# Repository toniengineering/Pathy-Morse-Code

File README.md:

Pathy is a small morse code device used to blink morse code with the click of a button. I wanted to try learning morse code a bit and having buttons where I can look at the light and whether it was a long blink or small blink I should be able to translate it. Also having a couple of premade buttons sounded cool like yes and no, they are always used and quick to learn. I decided to do a project like this because of how much I know how to code and I have not worked with pcbs before so I mostly wanted this to be about the pcbs design.

BOM:

 |Name        |Purpose      |Quantity                                                    |Total Cost (USD)|Link                                                                                                                                                                                                                                                                                                                                                                                                                                                                                                                                                                                                                                                                                                                                              |Distributor|
|------------|-------------|------------------------------------------------------------|----------------|--------------------------------------------------------------------------------------------------------------------------------------------------------------------------------------------------------------------------------------------------------------------------------------------------------------------------------------------------------------------------------------------------------------------------------------------------------------------------------------------------------------------------------------------------------------------------------------------------------------------------------------------------------------------------------------------------------------------------------------------------|----------|
|Resistors   |Keep the lights from burning out.|600                                     |2.56            |https://www.aliexpress.us/item/3256803089832670.html?spm=a2g0o.productlist.main.24.2bd0EUb3EUb3c2&aem_p4p_detail=202606111512134497445139988470000354431&algo_pvid=38693eea-0157-403c-9d6e-a28d685c63fa&algo_exp_id=38693eea-0157-403c-9d6e-a28d685c63fa-23&pdp_ext_f=%7B%22order%22%3A%22364%22%2C%22eval%22%3A%221%22%2C%22fromPage%22%3A%22search%22%7D&pdp_npi=6%40dis%21USD%212.56%212.56%21%21%212.56%212.56%21%402101e80317812159332583749eac1f%2112000030358692951%21sea%21US%210%21ABX%211%210%21n_tag%3A-29910%3Bd%3A27d5160c%3Bm03_new_user%3A-29895&curPageLogUid=imZQpjGjPpkV&utparam-url=scene%3Asearch%7Cquery_from%3A%7Cx_object_id%3A1005003276147422%7C_p_origin_prod%3A&search_p4p_id=202606111512134497445139988470000354431_7|Aliexpress|
|Xiao rp2040 |Power on the electronics for the pcb|1                                    |11.73           |https://www.aliexpress.us/item/3256807240972277.html?spm=a2g0o.productlist.0.0.1bc9379c5csoli&gatewayAdapt=glo2usa                                                                                                                                                                                                                                                                                                                                                                                                                                                                                                                                                                                                                                |Aliexpress|
|Keycaps     |To put on top of the key switches|8                                       |2.86            |https://www.aliexpress.us/item/3256810033104022.html?spm=a2g0o.productlist.main.35.52ceLShpLShp82&utparam-url=scene%3Asearch%7Cquery_from%3Apc_back_same_best%7Cx_object_id%3A1005010219418774%7C_p_origin_prod%3A&algo_pvid=1bf07656-f37d-443e-93b2-8f0d7e1feb6e&algo_exp_id=1bf07656-f37d-443e-93b2-8f0d7e1feb6e&pdp_ext_f=%7B%22order%22%3A%2252%22%2C%22fromPage%22%3A%22search%22%7D&pdp_npi=6%40dis%21USD%212.87%212.87%21%21%2119.37%2119.37%21%402103128917812050536722227e44ff%2112000051568483121%21sea%21US%210%21ABX%211%210%21n_tag%3A-29910%3Bd%3A27d5160c%3Bm03_new_user%3A-29895&gatewayAdapt=4itemAdapt|                                                                                                                         |Aliexpress|
|Key switches|So I can click it to make the lights blink the way I want.|10             |3.05            |https://www.aliexpress.us/item/3256810491600900.html?spm=a2g0n.shopcart.0.0.5f7438daR4t9Y4&mp=1&pdp_npi=6%40dis%21USD%21USD+6.10%21USD+3.05%21%21USD+3.05%21%21%21%402101e2b617812066391243237ea891%2112000053164128840%21ct%21US%21-1%21%211%210%21&gatewayAdapt=glo2usa                                                                                                                                                                                                                                                                                                                                                                                                                                                                         |Aliexpress|
|5mm LED     |The blinking every time I press a key switch|100                          |1.36            |https://www.aliexpress.us/item/3256805522196114.html?spm=a2g0o.productlist.main.13.2ed12c10o9N1kK&utparam-url=scene%3Asearch%7Cquery_from%3Apc_back_same_best%7Cx_object_id%3A1005005708510866%7C_p_origin_prod%3A&algo_pvid=f5e9e0e2-db45-43fd-8563-3f353d0a8ab3&algo_exp_id=f5e9e0e2-db45-43fd-8563-3f353d0a8ab3&pdp_ext_f=%7B%22order%22%3A%2214320%22%2C%22fromPage%22%3A%22search%22%7D&pdp_npi=6%40dis%21USD%211.36%211.36%21%21%219.14%219.14%21%402103128917812047619552862e44ff%2112000034078716878%21sea%21US%210%21ABX%211%210%21n_tag%3A-29910%3Bd%3A27d5160c%3Bm03_new_user%3A-29895&gatewayAdapt=4itemAdapt|                                                                                                                        |Aliexpress|
[convertcsv.md](https://github.com/user-attachments/files/28859285/convertcsv.md)

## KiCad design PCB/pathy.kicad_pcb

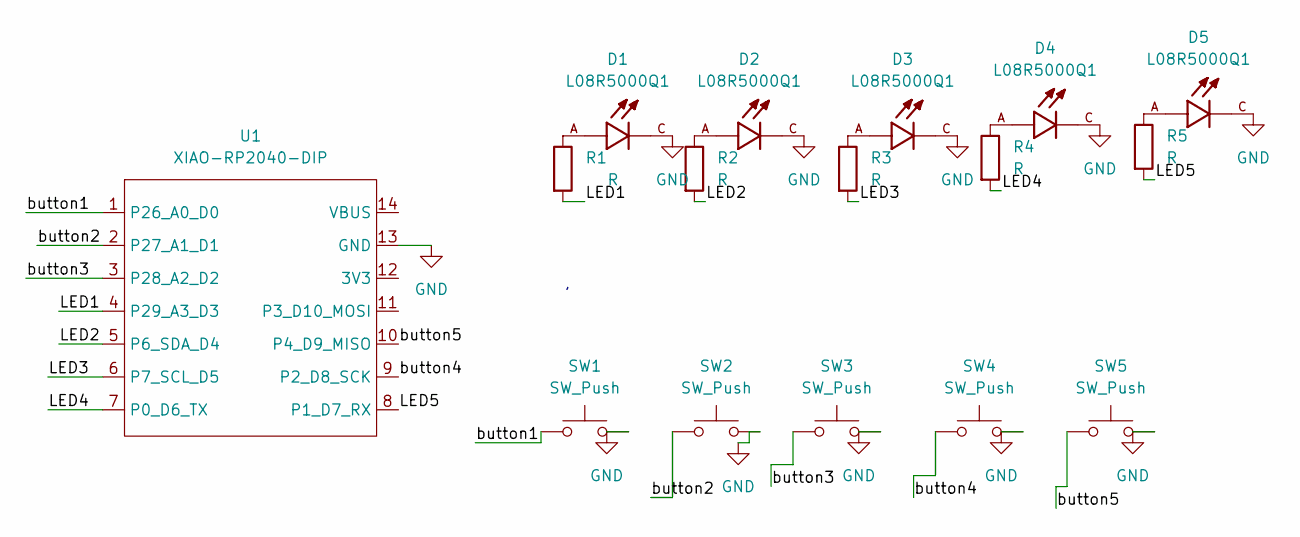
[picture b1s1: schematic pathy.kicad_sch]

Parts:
D1, D2, D3, D4, D5: L08R5000Q1; LEDRD254W57D500H1070; PARTREV NA
R1, R2, R3, R4, R5: R; R_Axial_DIN0204_L3.6mm_D1.6mm_P5.08mm_Horizontal
SW1, SW2, SW3, SW4, SW5: SW_Push; SW_Cherry_MX_1.00u_PCB
U1: XIAO-RP2040-DIP

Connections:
/LED1: R1.2, U1.4 (P29_A3_D3)
/LED2: R2.2, U1.5 (P6_SDA_D4)
/LED3: R3.2, U1.6 (P7_SCL_D5)
/LED4: R4.2, U1.7 (P0_D6_TX)
/LED5: R5.2, U1.8 (P1_D7_RX)
/button1: SW1.1, U1.1 (P26_A0_D0)
/button2: SW2.1, U1.2 (P27_A1_D1)
/button3: SW3.1, U1.3 (P28_A2_D2)
/button4: SW4.1, U1.9 (P2_D8_SCK)
/button5: SW5.1, U1.10 (P4_D9_MISO)
GND: D1.C, D2.C, D3.C, D4.C, D5.C, SW1.2, SW2.2, SW3.2, SW4.2, SW5.2, U1.13 (GND)
unnamed: D1.A, R1.1
unnamed: D2.A, R2.1
unnamed: D3.A, R3.1
unnamed: D4.A, R4.1
unnamed: D5.A, R5.1

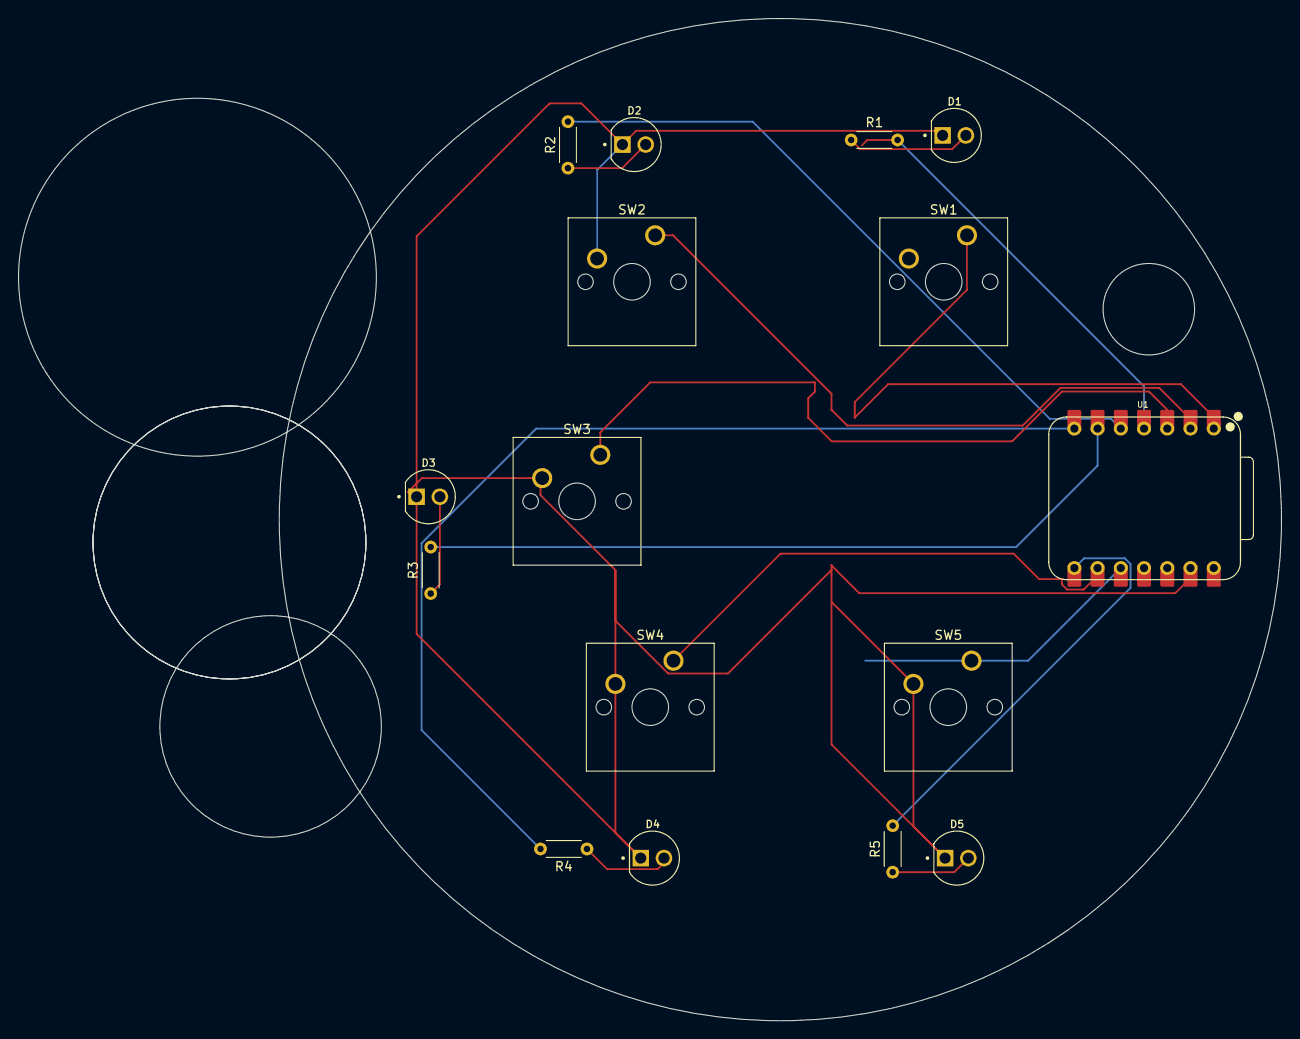
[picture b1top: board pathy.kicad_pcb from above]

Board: 2 copper layers, 138.1 x 109.6 mm, 16 parts (0 on the bottom side), 16 nets.

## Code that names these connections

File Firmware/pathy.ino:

#define BUT1 D0
#define BUT2 D1
#define BUT3 D2
#define BUT4 D8
#define BUT5 D9


#define LED1 D3
#define LED2 D4
#define LED3 D5
#define LED4 D6
#define LED5 D7

void setup() {
pinMode(BUT1, INPUT_PULLUP);
pinMode(BUT2, INPUT_PULLUP);
pinMode(BUT3, INPUT_PULLUP);
pinMode(BUT4, INPUT_PULLUP);
pinMode(BUT5, INPUT_PULLUP);


pinMode(LED1, OUTPUT);
pinMode(LED2, OUTPUT);
pinMode(LED3, OUTPUT);
pinMode(LED4, OUTPUT);
pinMode(LED5, OUTPUT);

}

void loop() {
  //small dash
 if (digitalRead(BUT1) == LOW) {
 digitalWrite(LED1, HIGH);
 delay(500);
 digitalWrite(LED1, LOW);
 delay(1000);
 }
 // long dash
 if
 (digitalRead(BUT2) == LOW) {
 digitalWrite(LED2, HIGH);
 delay(1000);
 digitalWrite(LED2, LOW);
 delay(1000);
 }
 //s
 if 
  (digitalRead(BUT3) == LOW) {
 digitalWrite(LED3, HIGH);
 delay(500);
 digitalWrite(LED3, LOW);
 delay(500);
 digitalWrite(LED3, HIGH);
delay(500);
digitalWrite(LED3, LOW);
delay(500);
digitalWrite(LED3, HIGH);
 delay(500);
 digitalWrite(LED3, LOW);
 delay(500);
 //o
 digitalWrite(LED3, HIGH);
 delay(1000);
 digitalWrite(LED3, LOW);
 delay(500);
  digitalWrite(LED3, HIGH);
 delay(1000);
 digitalWrite(LED3, LOW);
 delay(500);
  digitalWrite(LED3, HIGH);
 delay(1000);
 digitalWrite(LED3, LOW);
 delay(500);
 //s
 (digitalRead(BUT3) == LOW) ;
 digitalWrite(LED3, HIGH);
 delay(500);
 digitalWrite(LED3, LOW);
 delay(500);
 digitalWrite(LED3, HIGH);
delay(500);
digitalWrite(LED3, LOW);
delay(500);
digitalWrite(LED3, HIGH);
 delay(500);
 digitalWrite(LED3, LOW);
 delay(500);
  }
 //yes
if
  (digitalRead(BUT4) == LOW) {
 digitalWrite(LED4, HIGH);
 delay(1000);
 digitalWrite(LED4, LOW);
 delay(500);
 digitalWrite(LED4, HIGH);
 delay(500);
 digitalWrite(LED4, LOW);
 delay(500);
 digitalWrite(LED4, HIGH);
 delay(1000);
 digitalWrite(LED4, LOW);
 delay(500);
 digitalWrite(LED4, HIGH);
 delay(1000);
 digitalWrite(LED4, LOW);
 delay(1000);
 digitalWrite(LED4, HIGH);
 delay(500);
 digitalWrite(LED4, LOW);
 delay(1000);
 digitalWrite(LED4, HIGH);
 delay(500);
 digitalWrite(LED4, LOW);
 delay(500);
  digitalWrite(LED4, HIGH);
 delay(500);
 digitalWrite(LED4, LOW);
 delay(500);
  digitalWrite(LED4, HIGH);
 delay(500);
 digitalWrite(LED4, LOW);
 delay(500);
  }
 
 //no
if
  (digitalRead(BUT5) == LOW) {
 digitalWrite(LED5, HIGH);
 delay(1000);
 digitalWrite(LED5, LOW);
 delay(500);
 digitalWrite(LED5, HIGH);
 delay(500);
 digitalWrite(LED5, LOW);
 delay(1000);
 digitalWrite(LED5, HIGH);
 delay(1000);
 digitalWrite(LED5, LOW);
 delay(500);
 digitalWrite(LED5, HIGH);
 delay(1000);
 digitalWrite(LED5, LOW);
 delay(500);
 digitalWrite(LED5, HIGH);
 delay(1000);
 digitalWrite(LED5, LOW);
 delay(500);
}

else{
  digitalWrite(LED1, LOW);
  digitalWrite(LED2, LOW);
  digitalWrite(LED3, LOW);
  digitalWrite(LED4, LOW);
  digitalWrite(LED5, LOW);
}

}

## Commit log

2026-05-24 Create KICad
2026-05-24 Update KICad
2026-06-11 README.md
2026-06-11 Schematic
2026-06-11 Create ScematicFolder
2026-06-11 Create ijb
2026-06-11 Pics and link
2026-06-11 Create link
2026-06-11 Create pic
2026-06-11 Create Files
2026-06-11 Create Oi
2026-06-11 Create w
2026-06-11 Create x
2026-06-12 Create d
